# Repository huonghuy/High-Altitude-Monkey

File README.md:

# High-Altitude-Monkey (HAM)

HAM is a robotic monkey that flies on a high-altitude balloon. It moves, talks and
streams live video during flight, and is used for K-12 "near space" outreach on the
University of Bridgeport STEM bus. The project started in 2018 under a NASA USIP grant.
The 2024–2025 rebuild (HARM) adds new electronics, firmware and a controllable vent.
See the [ASEE 2025 paper](docs/papers/ASEE-2025/) for background.

## System overview

```
 Command Center ──(MC board)── Mega + HC-05 ))) Bluetooth ((( HC-05 + Mega ── ham radio ─┐
   (ground)                                                    (comms payload,          │
                                                                balloon)                │
                                                                                        │
                                                     ham-radio packets = commands       │
                                                                                        ▼
                                   HAM payload box ── Main board (Mega 2560 Pro)
                                     ├─ PCA9685 → servos (monkey movement)
                                     ├─ HC-05 ← commands from the comms payload
                                     ├─ 12 V switch → VideoLynx VM-70X video TX (on/off)
                                     └─ VL board on the VM-70X (RF power, camera, fan)
```

| Board | What it does | KiCad project |
|-------|--------------|---------------|
| **Main** | Primary board in the monkey box. Drives the servos, receives commands over Bluetooth from the comms payload, switches and controls the VideoLynx. | `hardware/kicad/Main` |
| **LM** (Land Module) | Used on the ground when HAM isn't flying. Connects the payload box to the command center over Bluetooth. | `hardware/kicad/LM` |
| **MC** (Mission Control) | Replacement for the old mission-control board in the command center. | `hardware/kicad/MC` |
| **VL** (VideoLynx) | Small board on top of the VM-70X video transmitter. Wired to Main with jumpers. | `hardware/kicad/VL` |
| **HC-05 Programmer** | Utility board for configuring the HC-05 Bluetooth modules. | `hardware/kicad/HC-05_Programmer` |

The comms payload (ham radio + Mega + HC-05) has no custom PCB.

**No HAM PCB has worked yet.** Read [`hardware/KNOWN_ISSUES.md`](hardware/KNOWN_ISSUES.md)
before ordering boards.

## Repository layout

```
hardware/
  kicad/            KiCad 10 projects (current source of truth for PCBs)
  easyeda-archive/  Original EasyEDA Standard files, all versions (read-only history)
  gerbers/          Fab outputs from past orders
  breadboard/       Early breadboard layout
  datasheets/       Part datasheets and module pinouts
  bom/              Parts list
  KNOWN_ISSUES.md   Open hardware bugs
firmware/
  Monkey_v2/            Flight firmware for the monkey (Main board, Mega 2560)
  Ground_Control/       Ground-station control sketch
  Telemetry_Processor/  Ground-side telemetry/APRS processing
  USIP_ver1_5_ESP/      ESP32 ground-station firmware (current)
  archive/              Older firmware versions (2019 USIP code, Monkey v1, USIP 1.1–1.4)
mechanical/         Body/arm STLs, MC panel (SolidWorks, 3MF, DXF)
docs/
  papers/ASEE-2025/   LaTeX source and PDF of the ASEE paper
  presentations/      Posters and slide decks (BERC 2024, NASA Minnesota, ASEE)
  flight-data/        Data from the 2025-06-05 flight
  images/             Photos, renders, diagrams
  usip-notes/         2019 USIP build notes and FAA documents
```

## Getting started

**Hardware:** Install [KiCad 10](https://www.kicad.org/) and open the `.kicad_pro` in
`hardware/kicad/<board>/`.

**Firmware (Mega boards):** Arduino IDE 2.x. Install the libraries listed in
`firmware/Monkey_v2/Libraries.txt` (Adafruit PWM Servo Driver, Adafruit BusIO), plus the
CH340 driver if you're using the Mega 2560 Pro module.

**Firmware (ESP32 ground station):** Arduino IDE with the ESP32 core. Needs Adafruit
BME280 and Adafruit Unified Sensor. See the notes at the top of
`firmware/USIP_ver1_5_ESP/USIP_ver1_5/Config.h`.

## Large files

Slide decks (`*.pptx`) are stored with [Git LFS](https://git-lfs.com). Run
`git lfs install` before cloning, or you'll get small pointer files instead of the decks.

## License

See [LICENSE](LICENSE).

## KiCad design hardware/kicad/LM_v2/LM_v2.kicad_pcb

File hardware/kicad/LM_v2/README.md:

# LM_v2: Land Module (ESP32)

Bluetooth Classic ↔ RS-232 bridge between the comms payload and Mission Control, built on an ESP32-WROOM-32E. It replaces the old ATmega2560 + HC-05 LM. Firmware is in `firmware/LM_v2`.

## Projects

| Project | Board |
|---|---|
| `LM_v2` | 36 × 55.3 mm, plus two M3 mounting ears (52 mm across) |
| `LM_v2_NoMount` | Same board, 36 × 55.3 mm, no ears |

`LM_v2.kicad_sch` is the master. `LM_v2_NoMount.kicad_sch` is a copy, and the NoMount PCB is LM_v2's board with the ears and M3 holes removed. After a change, copy both over and re-derive NoMount.

## Design notes

- Power: USB-C VBUS → PTC fuse F1 → TPS62162 3.3 V buck (U4, 2.2 µH L1, 10 µF in, 22 µF out). The buck is routed to TI's layout guide (SLVSAM2E §11). VOS senses +3V3 at C2.
- USB-UART: CH340C with two-transistor auto-reset into EN and IO0. USBLC6-2 ESD on the data lines.
- RS-232: MAX3232 to J2, an Assmann A-DS 09 A/KG-T2S (`HAM:DSUB-9_Male_Horizontal_Assmann_A-DS-KG`, drawing ASS 4888 CO in `hardware/datasheets/`). It is centred on the bottom edge with its two boardlock holes (Ø3.05 mm, 24.99 mm apart); the board edge sits at the flange, 7.2 mm from the pin 6–9 row.
- The ESP32 antenna overhangs the top edge. Keep metal away from it in the enclosure.
- Trace widths: 0.4 mm power class (VBUS, +3V3, GND), 0.2 mm signals, GND pours on both layers with stitching vias.

## Checks

Run from `hardware/kicad`:

```
python3 tools/check_netlist.py LM_v2/LM_v2.kicad_sch LM_v2/pin_nets.csv   # every pin's net vs the design table
kicad-cli sch erc LM_v2/LM_v2.kicad_sch
kicad-cli pcb drc --schematic-parity LM_v2/LM_v2.kicad_pcb
```

All three were clean on 2026-11-25. If you change a net on purpose, update `pin_nets.csv` as well.

## Connection to Mission Control

J2 plugs into MC's Telemetry Processor port (`Serial2`, a female DE-9 described in the firmware as "PC, for telemetry Processor"), either directly or through the existing 6 ft male-to-female cable. J2 is a male DE-9 wired like a PC: pin 2 = LM receive, pin 3 = LM transmit, pin 5 = GND. This matches the ground-station setup in `docs/` (the grey box next to the Command Processor).

## Parts

Every part has a manufacturer and part number in the schematic (`Manufacturer`, `MPN` fields). The boards are hand-assembled. U4 (TPS62162, WSON) and the ESP32's ground pad both need hot air or the hotplate. TP1–TP3 are bare pads and are not on the BOM.

## Open before ordering

Fab packages (Gerbers, drill, BOM, assembly PDFs) are in `hardware/gerbers/LM_v2/` and `hardware/gerbers/LM_v2_NoMount/`.

- **J2 footprint:** drawn from the Assmann drawing, reading its "7.2 mm footprint" as board edge to the pin 6–9 row. Check it against a real connector before a large order.
- **Bluetooth pairing:** the firmware waits as a slave, so the payload HC-05 has to be set as master and bound to the LM's address. See `firmware/LM_v2/README.md`.
- **Board-level details:** R2's reference label is on the Fab layer only, because the silkscreen had no room for it.

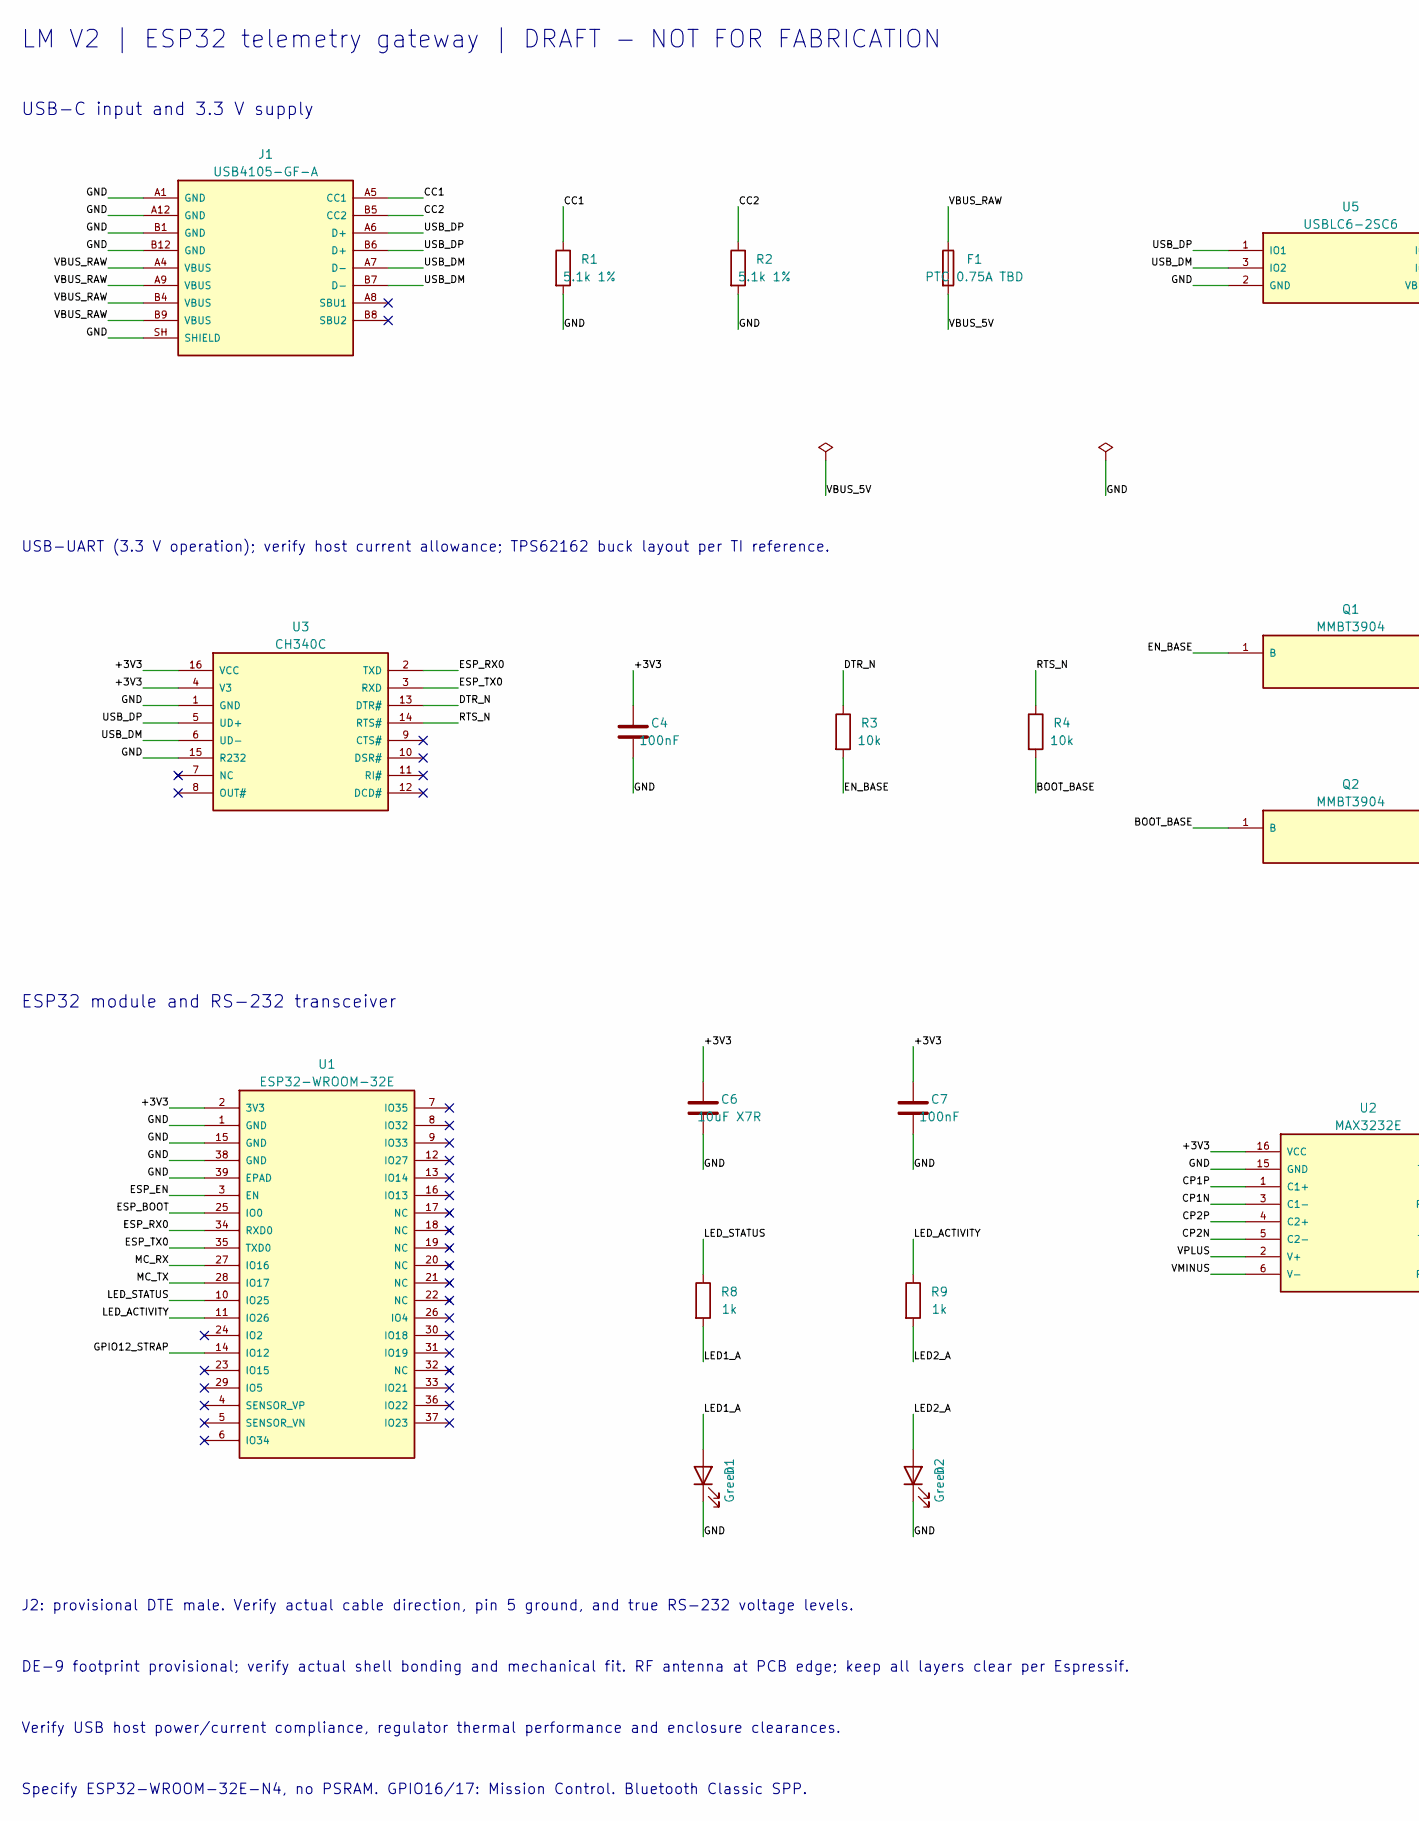
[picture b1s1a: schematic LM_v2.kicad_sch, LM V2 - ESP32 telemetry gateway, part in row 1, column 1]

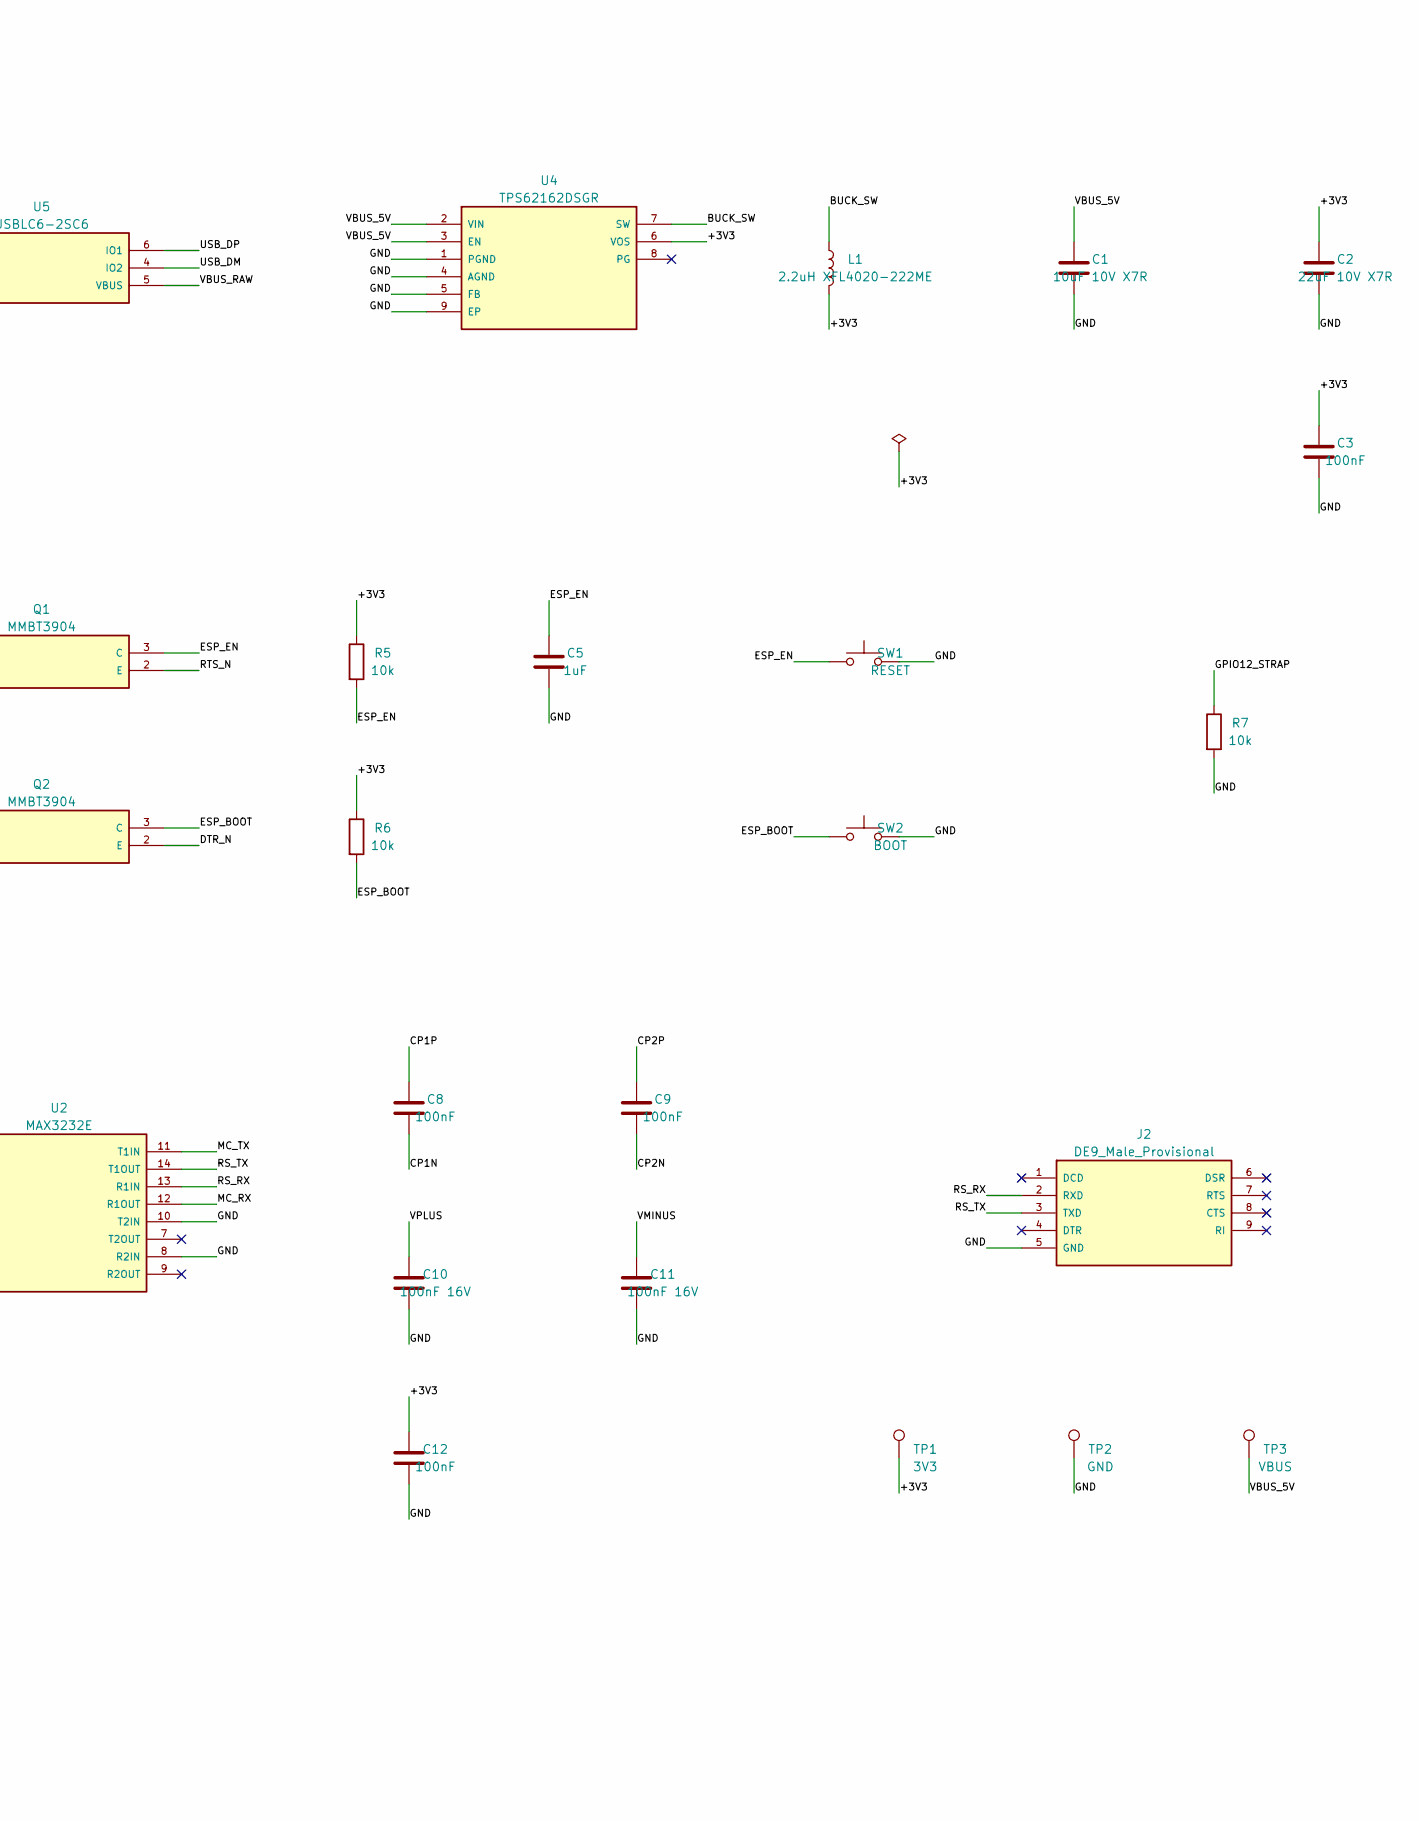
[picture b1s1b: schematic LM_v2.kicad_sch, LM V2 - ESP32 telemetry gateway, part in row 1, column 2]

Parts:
C1: 10uF 10V X7R; C_0805_2012Metric
C2: 22uF 10V X7R; C_1206_3216Metric
C3, C4, C7, C8, C9, C12: 100nF; C_0603_1608Metric
C5: 1uF; C_0603_1608Metric
C6: 10uF X7R; C_0805_2012Metric
C10, C11: 100nF 16V; C_0603_1608Metric
D1, D2: Green; LED_0603_1608Metric
F1: PTC 0.75A TBD; Fuse_1206_3216Metric
J1: USB4105-GF-A; USB_C_Receptacle_GCT_USB4105-xx-A_16P_TopMnt_Horizontal
J2: DE9_Male_Provisional; DSUB-9_Male_Horizontal_BoardEdge
L1: 2.2uH XFL4020-222ME; L_Coilcraft_XxL4020
Q1, Q2: MMBT3904; SOT-23
R1, R2: 5.1k 1%; R_0603_1608Metric
R3, R4, R5, R6, R7: 10k; R_0603_1608Metric
R8, R9: 1k; R_0603_1608Metric
SW1: RESET; SW_SPST_TL3342
SW2: BOOT; SW_SPST_TL3342
TP1: 3V3; TestPoint_Pad_D1.5mm
TP2: GND; TestPoint_Pad_D1.5mm
TP3: VBUS; TestPoint_Pad_D1.5mm
U1: ESP32-WROOM-32E
U2: MAX3232E; SOIC-16_3.9x9.9mm_P1.27mm
U3: CH340C; SOIC-16_3.9x9.9mm_P1.27mm
U4: TPS62162DSGR; WSON-8-1EP_2x2mm_P0.5mm_EP0.9x1.6mm_ThermalVias
U5: USBLC6-2SC6; SOT-23-6

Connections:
/+3V3: C2.1, C3.1, C4.1, C6.1, C7.1, C12.1, L1.2, R5.1, R6.1, TP1.1 (1_1), U1.2 (3V3), U2.16 (VCC), U3.4 (V3), U3.16 (VCC), U4.6 (VOS)
/BOOT_BASE: Q2.1 (B), R4.2
/BUCK_SW: L1.1, U4.7 (SW)
/CC1: J1.A5 (CC1), R1.1
/CC2: J1.B5 (CC2), R2.1
/CP1N: C8.2, U2.3 (C1-)
/CP1P: C8.1, U2.1 (C1+)
/CP2N: C9.2, U2.5 (C2-)
/CP2P: C9.1, U2.4 (C2+)
/DTR_N: Q2.2 (E), R3.1, U3.13 (DTR#)
/EN_BASE: Q1.1 (B), R3.2
/ESP_BOOT: Q2.3 (C), R6.2, SW2.1, U1.25 (IO0)
/ESP_EN: C5.1, Q1.3 (C), R5.2, SW1.1, U1.3 (EN)
/ESP_RX0: U1.34 (RXD0), U3.2 (TXD)
/ESP_TX0: U1.35 (TXD0), U3.3 (RXD)
/GND: C1.2, C2.2, C3.2, C4.2, C5.2, C6.2, C7.2, C10.2, C11.2, C12.2, D1.1 (K), D2.1 (K), J1.A1 (GND), J1.A12 (GND), J1.B1 (GND), J1.B12 (GND), J1.SH (SHIELD), J2.5 (GND), R1.2, R2.2, R7.2, SW1.2, SW2.2, TP2.1 (1_1), U1.1 (GND), U1.15 (GND), U1.38 (GND), U1.39 (EPAD), U2.8 (R2IN), U2.10 (T2IN), U2.15 (GND), U3.1 (GND), U3.15 (R232), U4.1 (PGND), U4.4 (AGND), U4.5 (FB), U4.9 (EP), U5.2 (GND)
/GPIO12_STRAP: R7.1, U1.14 (IO12)
/LED1_A: D1.2 (A), R8.2
/LED2_A: D2.2 (A), R9.2
/LED_ACTIVITY: R9.1, U1.11 (IO26)
/LED_STATUS: R8.1, U1.10 (IO25)
/MC_RX: U1.27 (IO16), U2.12 (R1OUT)
/MC_TX: U1.28 (IO17), U2.11 (T1IN)
/RS_RX: J2.2 (RXD), U2.13 (R1IN)
/RS_TX: J2.3 (TXD), U2.14 (T1OUT)
/RTS_N: Q1.2 (E), R4.1, U3.14 (RTS#)
/USB_DM: J1.A7 (D-), J1.B7 (D-), U3.6 (UD-), U5.3 (IO2), U5.4 (IO2)
/USB_DP: J1.A6 (D+), J1.B6 (D+), U3.5 (UD+), U5.1 (IO1), U5.6 (IO1)
/VBUS_5V: C1.1, F1.2, TP3.1 (1_1), U4.2 (VIN), U4.3 (EN)
/VBUS_RAW: F1.1, J1.A4 (VBUS), J1.A9 (VBUS), J1.B4 (VBUS), J1.B9 (VBUS), U5.5 (VBUS)
/VMINUS: C11.1, U2.6 (V-)
/VPLUS: C10.1, U2.2 (V+)

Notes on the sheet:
J2: provisional DTE male. Verify actual cable direction, pin 5 ground, and true RS-232 voltage levels.
USB-UART (3.3 V operation); verify host current allowance; TPS62162 buck layout per TI reference.
USB-C input and 3.3 V supply
Specify ESP32-WROOM-32E-N4, no PSRAM. GPIO16/17: Mission Control. Bluetooth Classic SPP.
ESP32 module and RS-232 transceiver
DE-9 footprint provisional; verify actual shell bonding and mechanical fit. RF antenna at PCB edge; keep all layers clear per Espressif.
LM V2 | ESP32 telemetry gateway | DRAFT - NOT FOR FABRICATION
Verify USB host power/current compliance, regulator thermal performance and enclosure clearances.

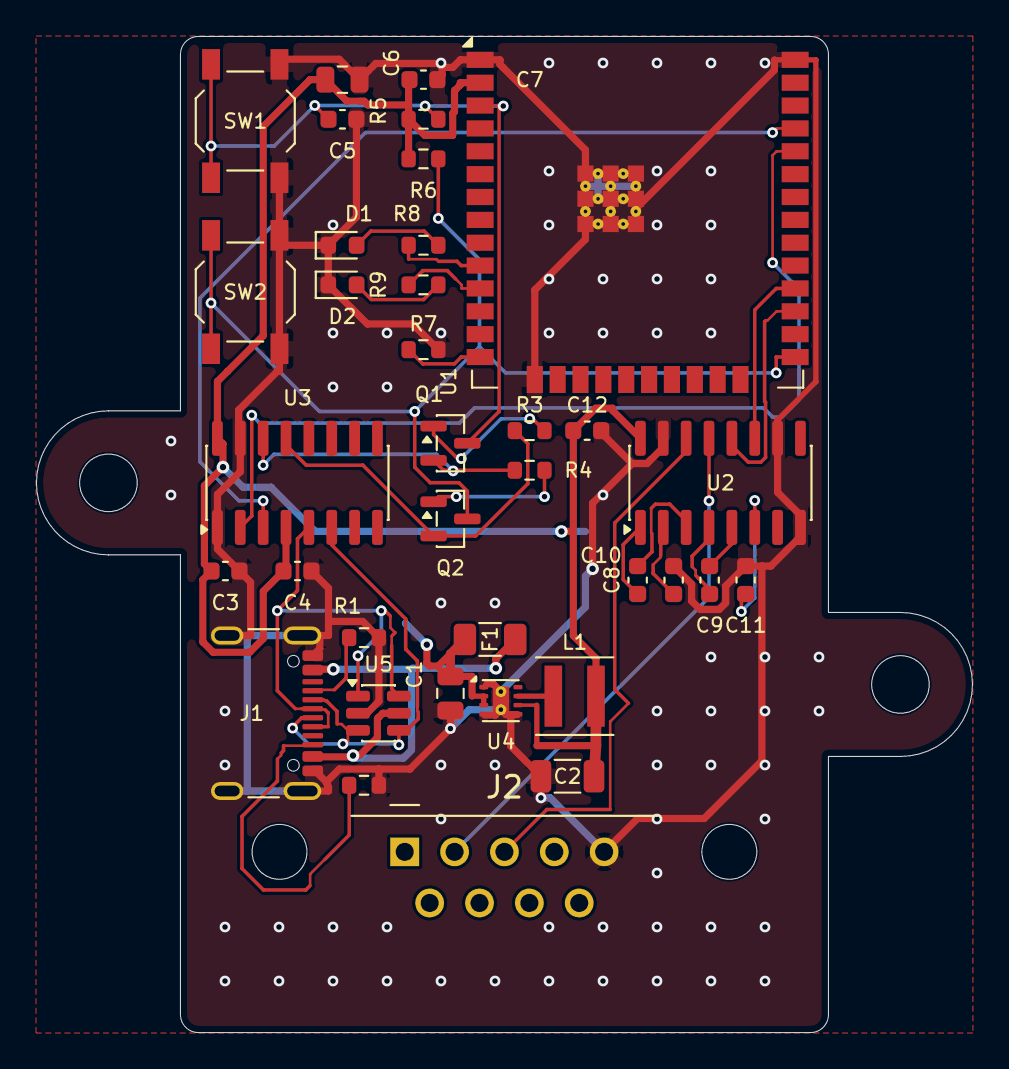
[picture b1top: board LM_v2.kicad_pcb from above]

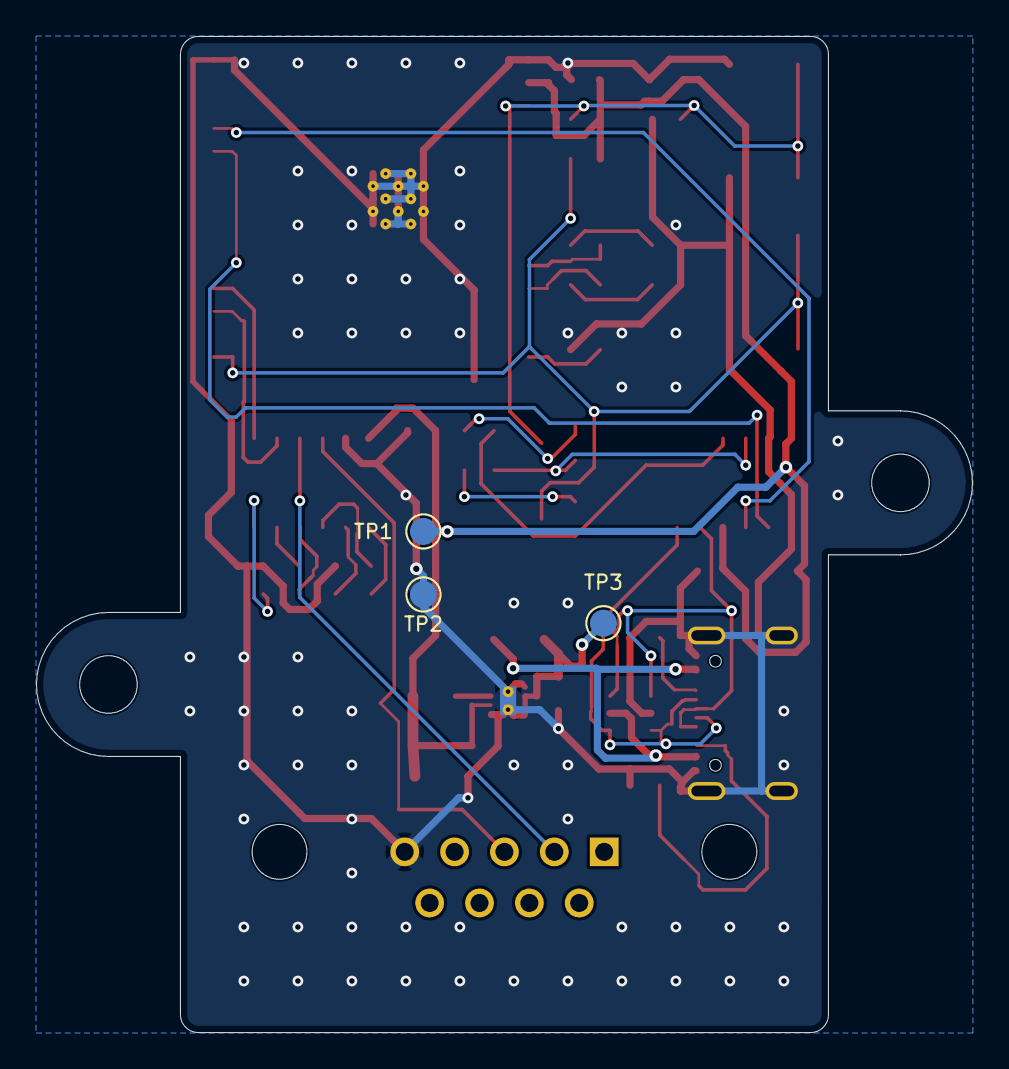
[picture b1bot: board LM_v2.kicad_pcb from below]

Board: 2 copper layers, 52.0 x 55.3 mm, 41 parts (3 on the bottom side), 32 nets.

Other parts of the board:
H1, H2: M3; MountingHole_3.2mm_M3

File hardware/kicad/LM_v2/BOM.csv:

Reference,Value,Footprint,Fit
J1,USB4105-GF-A,Connector_USB:USB_C_Receptacle_GCT_USB4105-xx-A_16P_TopMnt_Horizontal,Fit
R1,5.1k 1%,Resistor_SMD:R_0603_1608Metric,Fit
R2,5.1k 1%,Resistor_SMD:R_0603_1608Metric,Fit
F1,PTC 0.75A TBD,Fuse:Fuse_1206_3216Metric,Fit
U5,USBLC6-2SC6,Package_TO_SOT_SMD:SOT-23-6,Fit
U4,TPS62162DSGR,Package_SON:WSON-8-1EP_2x2mm_P0.5mm_EP0.9x1.6mm_ThermalVias,Fit
L1,2.2uH XFL4020-222ME,Inductor_SMD:L_Coilcraft_XxL4020,Fit
C1,10uF 10V X7R,Capacitor_SMD:C_0805_2012Metric,Fit
C2,22uF 10V X7R,Capacitor_SMD:C_1206_3216Metric,Fit
C3,100nF,Capacitor_SMD:C_0603_1608Metric,Fit
U3,CH340C,Package_SO:SOIC-16_3.9x9.9mm_P1.27mm,Fit
C4,100nF,Capacitor_SMD:C_0603_1608Metric,Fit
R3,10k,Resistor_SMD:R_0603_1608Metric,Fit
R4,10k,Resistor_SMD:R_0603_1608Metric,Fit
Q1,MMBT3904,Package_TO_SOT_SMD:SOT-23,Fit
Q2,MMBT3904,Package_TO_SOT_SMD:SOT-23,Fit
R5,10k,Resistor_SMD:R_0603_1608Metric,Fit
R6,10k,Resistor_SMD:R_0603_1608Metric,Fit
C5,1uF,Capacitor_SMD:C_0603_1608Metric,Fit
SW1,RESET,Button_Switch_SMD:SW_SPST_TL3342,Fit
SW2,BOOT,Button_Switch_SMD:SW_SPST_TL3342,Fit
R7,10k,Resistor_SMD:R_0603_1608Metric,Fit
U1,ESP32-WROOM-32E,RF_Module:ESP32-WROOM-32E,Fit
C6,10uF X7R,Capacitor_SMD:C_0805_2012Metric,Fit
C7,100nF,Capacitor_SMD:C_0603_1608Metric,Fit
R8,1k,Resistor_SMD:R_0603_1608Metric,Fit
R9,1k,Resistor_SMD:R_0603_1608Metric,Fit
D1,Green,LED_SMD:LED_0603_1608Metric,Fit
D2,Green,LED_SMD:LED_0603_1608Metric,Fit
U2,MAX3232E,Package_SO:SOIC-16_3.9x9.9mm_P1.27mm,Fit
C8,100nF,Capacitor_SMD:C_0603_1608Metric,Fit
C9,100nF,Capacitor_SMD:C_0603_1608Metric,Fit
C10,100nF 16V,Capacitor_SMD:C_0603_1608Metric,Fit
C11,100nF 16V,Capacitor_SMD:C_0603_1608Metric,Fit
C12,100nF,Capacitor_SMD:C_0603_1608Metric,Fit
J2,DE9_Male_Provisional,Connector_Dsub:DSUB-9_Pins_Horizontal_P2.77x2.84mm_EdgePinOffset9.40mm,Fit
TP1,3V3,TestPoint:TestPoint_Pad_D1.5mm,Fit
TP2,GND,TestPoint:TestPoint_Pad_D1.5mm,Fit
TP3,VBUS,TestPoint:TestPoint_Pad_D1.5mm,Fit

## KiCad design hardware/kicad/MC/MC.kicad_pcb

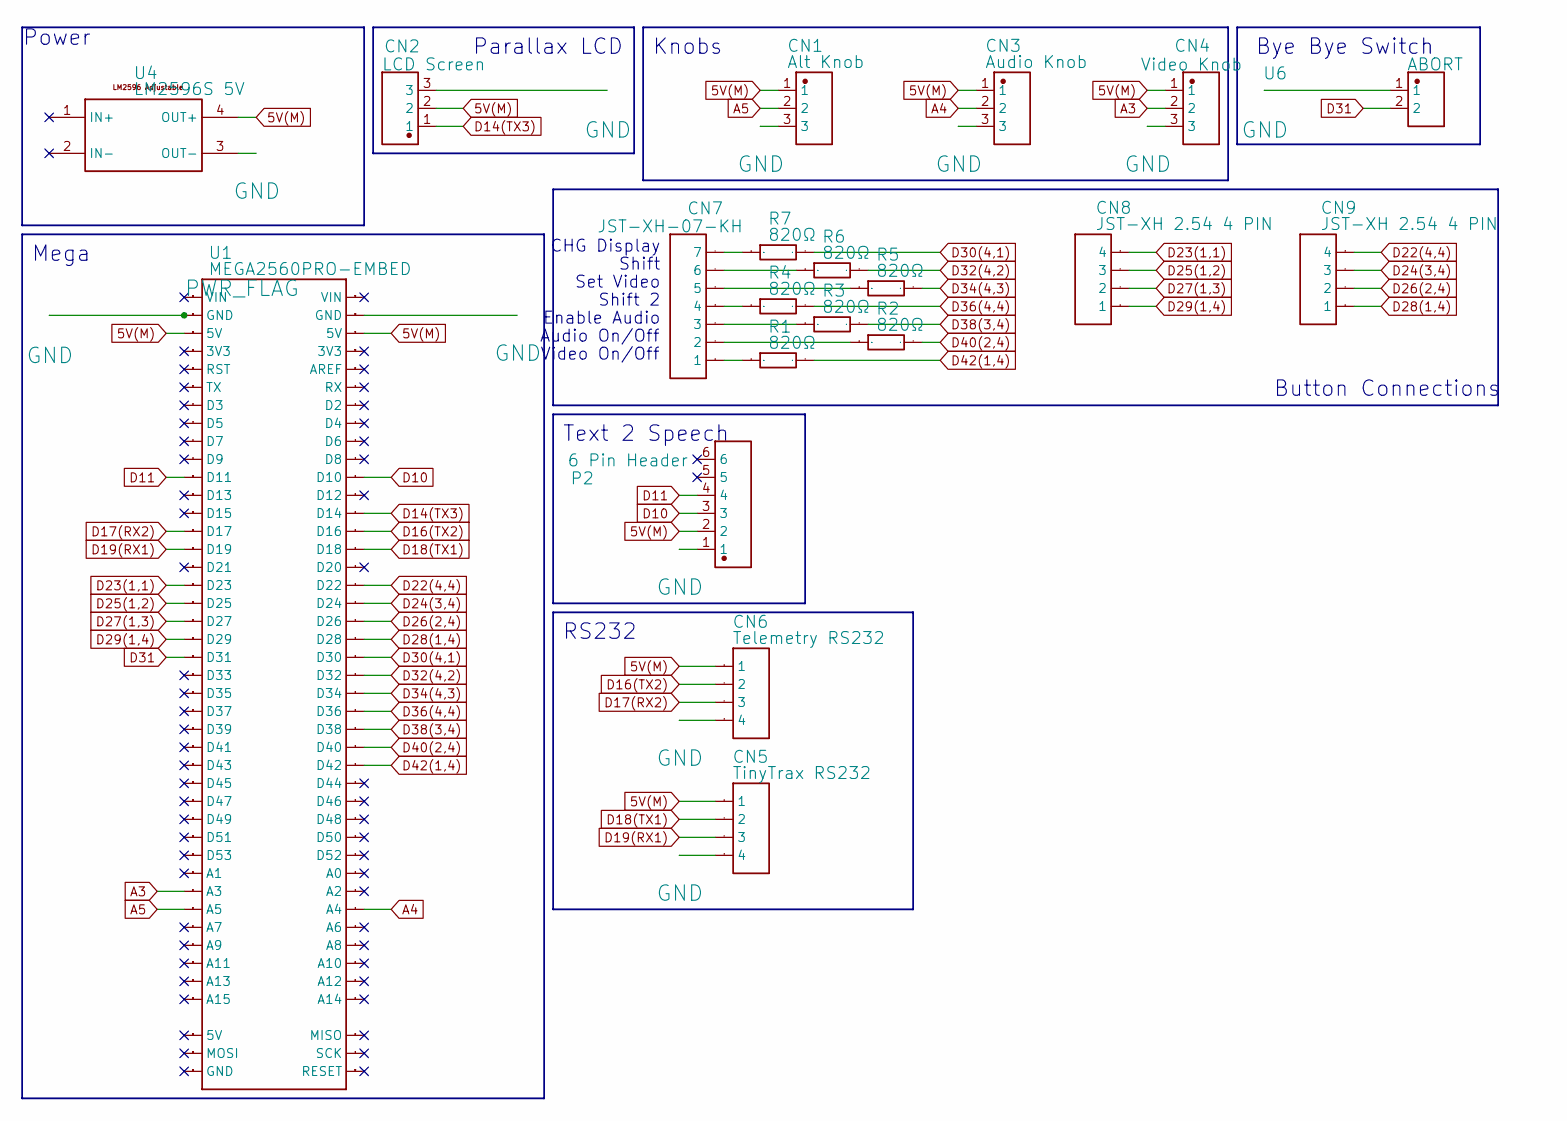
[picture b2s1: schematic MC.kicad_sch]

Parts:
CN1: Alt Knob; JST_XH_B3B-XH-A_1x03_P2.50mm_Vertical; Manufacturer Part XH插座1*3P间距2.5mm直针,
CN2: LCD Screen; JST_XH_B3B-XH-A_1x03_P2.50mm_Vertical; Manufacturer Part XH插座1*3P间距2.5mm直针,
CN3: Audio Knob; JST_XH_B3B-XH-A_1x03_P2.50mm_Vertical; Manufacturer Part XH插座1*3P间距2.5mm直针,
CN4: Video Knob; JST_XH_B3B-XH-A_1x03_P2.50mm_Vertical; Manufacturer Part XH插座1*3P间距2.5mm直针,
CN5: TinyTrax RS232; JST_XH_B4B-XH-A_1x04_P2.50mm_Vertical
CN6: Telemetry RS232; JST_XH_B4B-XH-A_1x04_P2.50mm_Vertical
CN7: JST-XH-07-KH; JST_XH_B7B-XH-A_1x07_P2.50mm_Vertical; Manufacturer Part JST-XH-04
CN8, CN9: JST-XH 2.54 4 PIN; JST_XH_B4B-XH-A_1x04_P2.50mm_Vertical
P2: 6 Pin Header; PinSocket_1x06_P2.54mm_Vertical; Manufacturer Part 2.54-1*6P母
R1, R2, R3, R4, R5, R6, R7: 820Ω; R_0402_1005Metric; Manufacturer Part RC0402JR-07820RL
U1: MEGA2560PRO-EMBED; Mega2560_Pro_Embed
U4: LM2596S 5V; LM2596_Module
U6: ABORT; JST_XH_B2B-XH-A_1x02_P2.50mm_Vertical; Manufacturer Part XH-2P-2.54

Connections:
5V(M): CN1.1, CN2.2, CN3.1, CN4.1, CN5.1, CN6.1, P2.2, U1.5V@1 (5V), U1.5V@2 (5V), U4.4 (OUT+)
A3: CN4.2, U1.A3
A4: CN3.2, U1.A4
A5: CN1.2, U1.A5
D10: P2.3, U1.D10
D11: P2.4, U1.D11
D14(TX3): CN2.1, U1.D14
D16(TX2): CN6.2, U1.D16
D17(RX2): CN6.3, U1.D17
D18(TX1): CN5.2, U1.D18
D19(RX1): CN5.3, U1.D19
D22(4,4): CN9.4, U1.D22
D23(1,1): CN8.4, U1.D23
D24(3,4): CN9.3, U1.D24
D25(1,2): CN8.3, U1.D25
D26(2,4): CN9.2, U1.D26
D27(1,3): CN8.2, U1.D27
D28(1,4): CN9.1, U1.D28
D29(1,4): CN8.1, U1.D29
D30(4,1): R7.2, U1.D30
D31: U1.D31, U6.2
D32(4,2): R6.2, U1.D32
D34(4,3): R5.2, U1.D34
D36(4,4): R4.2, U1.D36
D38(3,4): R3.2, U1.D38
D40(2,4): R2.2, U1.D40
D42(1,4): R1.2, U1.D42
GND: CN1.3, CN2.3, CN3.3, CN4.3, CN5.4, CN6.4, P2.1, U1.GND@1 (GND), U1.GND@2 (GND), U4.3 (OUT-), U6.1
unnamed: CN7.1, R1.1
unnamed: CN7.2, R2.1
unnamed: CN7.3, R3.1
unnamed: CN7.4, R4.1
unnamed: CN7.5, R5.1
unnamed: CN7.6, R6.1
unnamed: CN7.7, R7.1

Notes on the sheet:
Knobs
Video On/Off
Parallax LCD
RS232
Set Video
Button Connections
Shift
Bye Bye Switch
Shift 2
Text 2 Speech
Power
Enable Audio
Mega
CHG Display
Audio On/Off

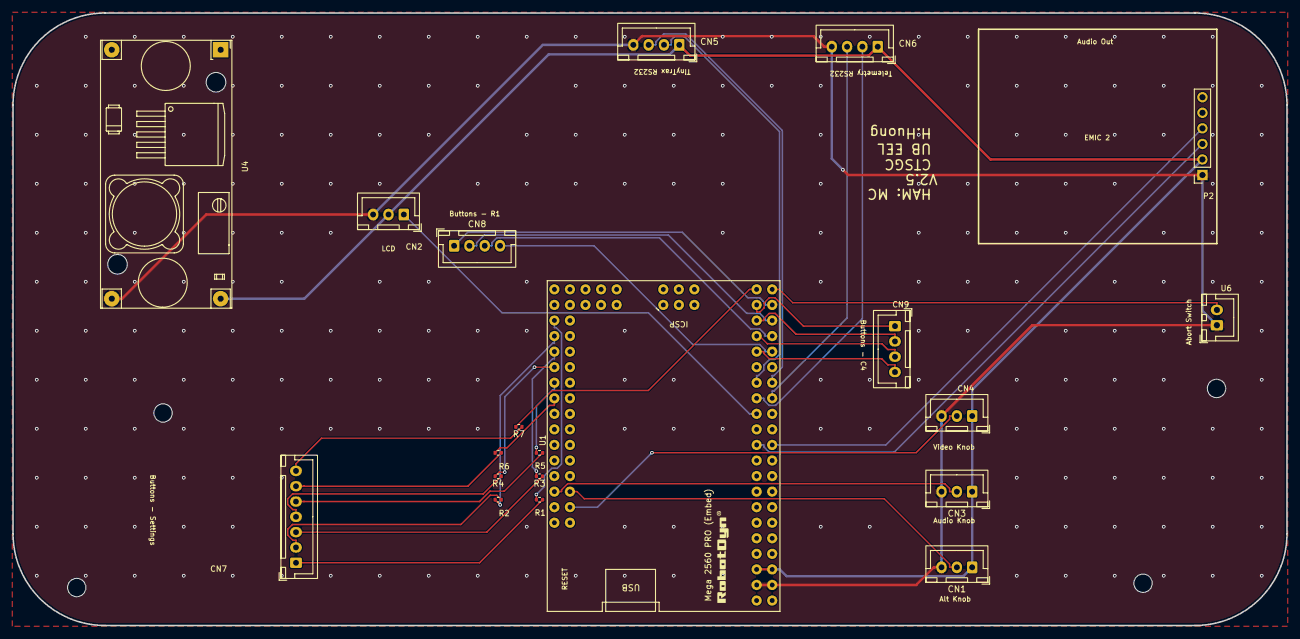
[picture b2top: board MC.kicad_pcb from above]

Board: 2 copper layers, 208.0 x 100.0 mm, 24 parts (0 on the bottom side), 35 nets.

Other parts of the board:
H2, H3, H4, H6: Hole 3mm; MountingHole_3mm

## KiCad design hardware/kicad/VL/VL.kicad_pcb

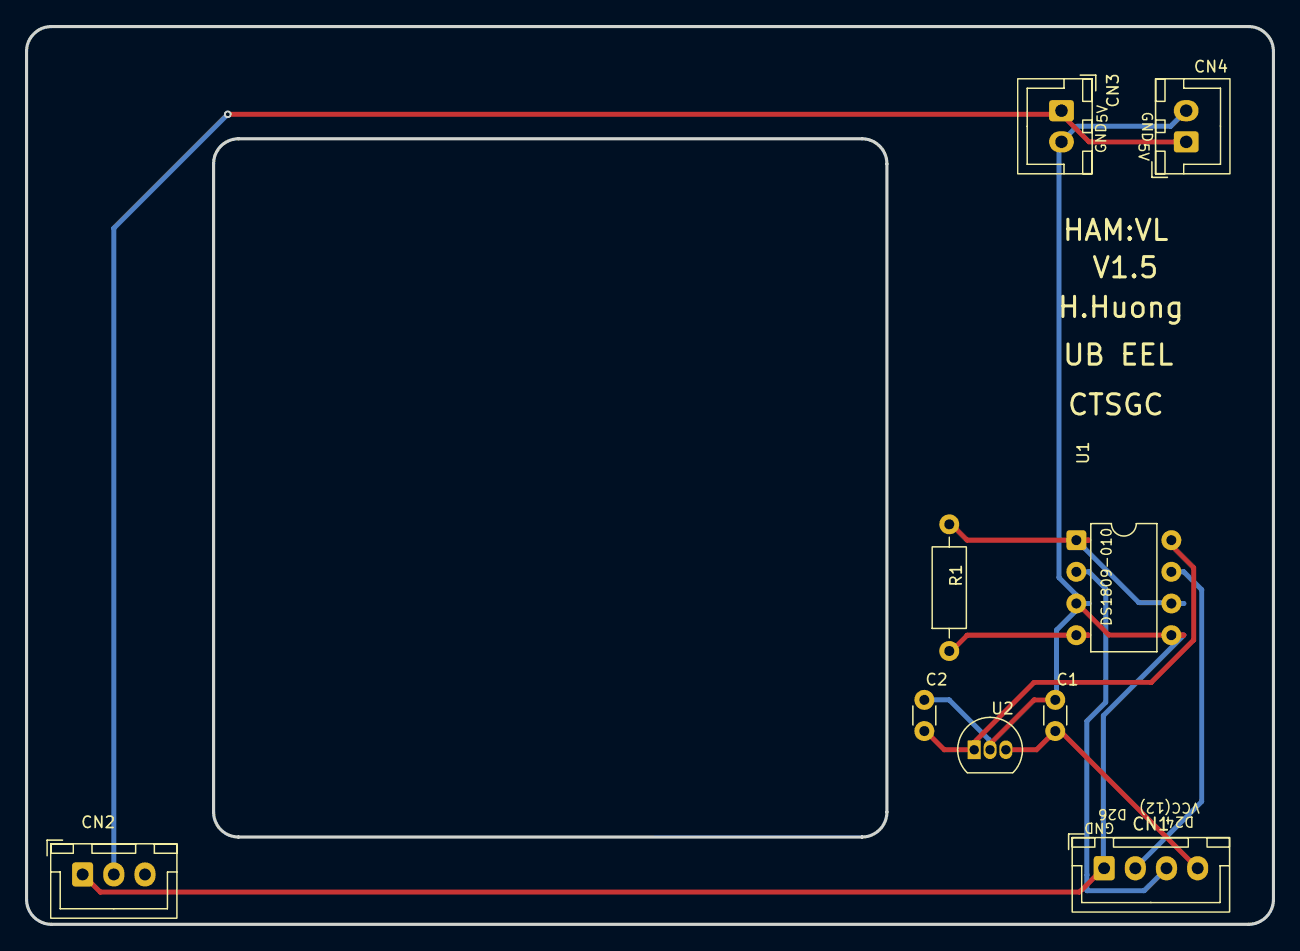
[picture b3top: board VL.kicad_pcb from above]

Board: 2 copper layers, 100.0 x 72.0 mm, 9 parts (0 on the bottom side), 8 nets.

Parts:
C1: 0.33uF; C_Disc_D3.0mm_W1.6mm_P2.50mm
C2: 0.1uF; C_Disc_D3.0mm_W1.6mm_P2.50mm
CN1: JST-XH2.5; JST_XH_B4B-XH-A_1x04_P2.50mm_Vertical
CN2: VideoLynx Fan; JST_XH_B3B-XH-A_1x03_P2.50mm_Vertical
CN3: Camera; JST_XH_B2B-XH-A_1x02_P2.50mm_Vertical
CN4: VL Power; JST_XH_B2B-XH-A_1x02_P2.50mm_Vertical
R1: 12kΩ; R_Axial_DIN0207_L6.3mm_D2.5mm_P10.16mm_Horizontal
U1: DS1809-010 10k Digital Pot; DIP-8_W7.62mm
U2: L78L05 (5 V, 100 mA); TO-92_Inline

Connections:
/5V: CN2.2, CN3.1, CN4.1
/5V_DS: C2.1, U1.8, U2.1
/D24: CN1.3, U1.2
/D26: CN1.2, U1.7
/VCC(12): C1.1, CN1.4, U2.3
GND: C1.2, C2.2, CN1.1, CN2.1, CN3.2, CN4.2, U1.3, U1.5, U2.2
unnamed: R1.2, U1.1, U1.6
unnamed: R1.1, U1.4

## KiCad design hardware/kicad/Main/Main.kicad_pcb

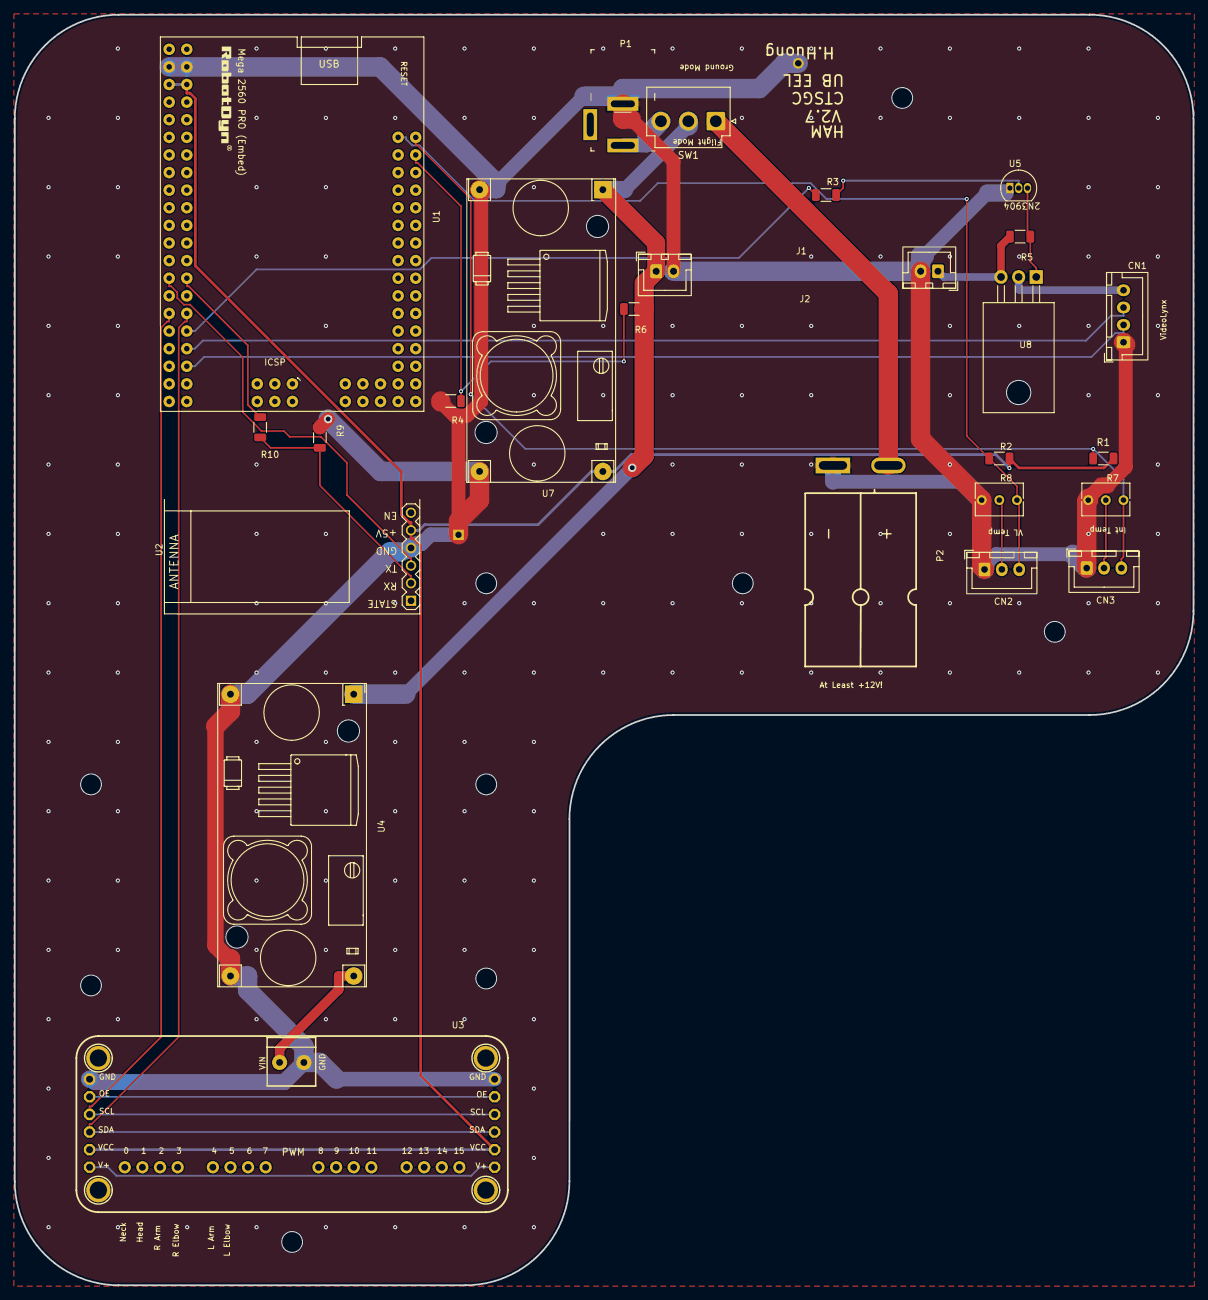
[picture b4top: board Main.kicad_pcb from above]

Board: 2 copper layers, 170.0 x 183.2 mm, 36 parts (0 on the bottom side), 23 nets.

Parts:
CN1: JST-XH2.5; JST_XH_B4B-XH-A_1x04_P2.50mm_Vertical
CN2: VideoLynx LM135H; JST_XH_B3B-XH-A_1x03_P2.50mm_Vertical
CN3: Int LM135H; JST_XH_B3B-XH-A_1x03_P2.50mm_Vertical
H1, H2, H3, H4, H7, H9, H10, H11, H12: Hole 3mm; MountingHole_3mm
J1: Pololu IN; JST_XH_B2B-XH-A_1x02_P2.50mm_Vertical
J2: Pololu OUT 13V; JST_XH_B2B-XH-A_1x02_P2.50mm_Vertical
P1: DC barrel jack 2.1mm; DC_Barrel_Jack_2.1mm
P2: PowerPole; Anderson_PowerPole_1327_Pair_Horizontal
R1, R2: 1.5kΩ; R_1206_3216Metric
R3: 3.3kΩ; R_1206_3216Metric
R4: 3.9kΩ; R_1206_3216Metric
R5: 8.2kΩ; R_1206_3216Metric
R6: 10kΩ; R_1206_3216Metric
R7, R8: 10kΩ; Potentiometer_Bourns_3266Y_Vertical
R9: 2kΩ; R_1206_3216Metric
R10: 1kΩ; R_1206_3216Metric
SW1: ON-OFF-ON Toggle (off-board); JST_VH_B3P-VH_1x03_P3.96mm_Vertical
U1: MEGA2560PRO-EMBED; Mega2560_Pro_Embed
U2: HC-05; HC-05_Module
U3: PCA9685; PCA9685_Breakout_Adafruit
U4: LM2596S 6V; LM2596_Module
U5: 2N3904; TO-92_Inline
U7: LM2596S 5V; LM2596_Module
U8: IRF9540N_FLAT; TO-220-3_Horizontal_TabDown
WP1: Wire pad; Pad_THT_Wire_D0.96mm
WP2: Wire pad; Pad_THT_Wire_D0.91mm

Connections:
5V(M): R1.1, R2.1, U1.5V@1, U1.5V@2, U2.5, U3.7 (VCC), U7.4
A0: CN3.3, R1.2, R7.3, U1.A0
A1: CN2.3, R2.2, R8.3, U1.A1
A2: R4.2, R6.2, U1.A2
D16(TX2): R10.1, U1.D16
D17(RX2): U1.D17, U2.3
D20(SDA): U1.D20, U3.6 (SDA)
D21(SCL): U1.D21, U3.5 (SCL)
D22: R3.1, U1.D22
D24: CN1.3, U1.D24
D26: CN1.2, U1.D26
GND: CN1.1, CN2.1, CN3.1, J1.2, J2.2, P1.2, P2.1, R4.1, R7.1, R8.1, R9.1, U1.GND@1, U1.GND@2, U2.4, U3.2 (GND), U3.3 (GND), U4.2, U4.3, U5.1 (E), U7.2, U7.3, WP1.2, WP2.1
unnamed: CN2.2, R8.2
unnamed: CN3.2, R7.2
unnamed: P2.2, SW1.1
unnamed: P1.1, SW1.3
unnamed: R9.2, R10.2, U2.2
unnamed: R3.2, U5.2 (B)
unnamed: R5.1, U5.3 (C), U8.1 (G)
Switch(12): CN1.4, U8.2 (D)
VCC: J1.1, R6.1, SW1.2, U4.1, U7.1
VCC(6): U3.1 (VIN), U4.4
VCC(12): J2.1, R5.2, U8.3 (S)

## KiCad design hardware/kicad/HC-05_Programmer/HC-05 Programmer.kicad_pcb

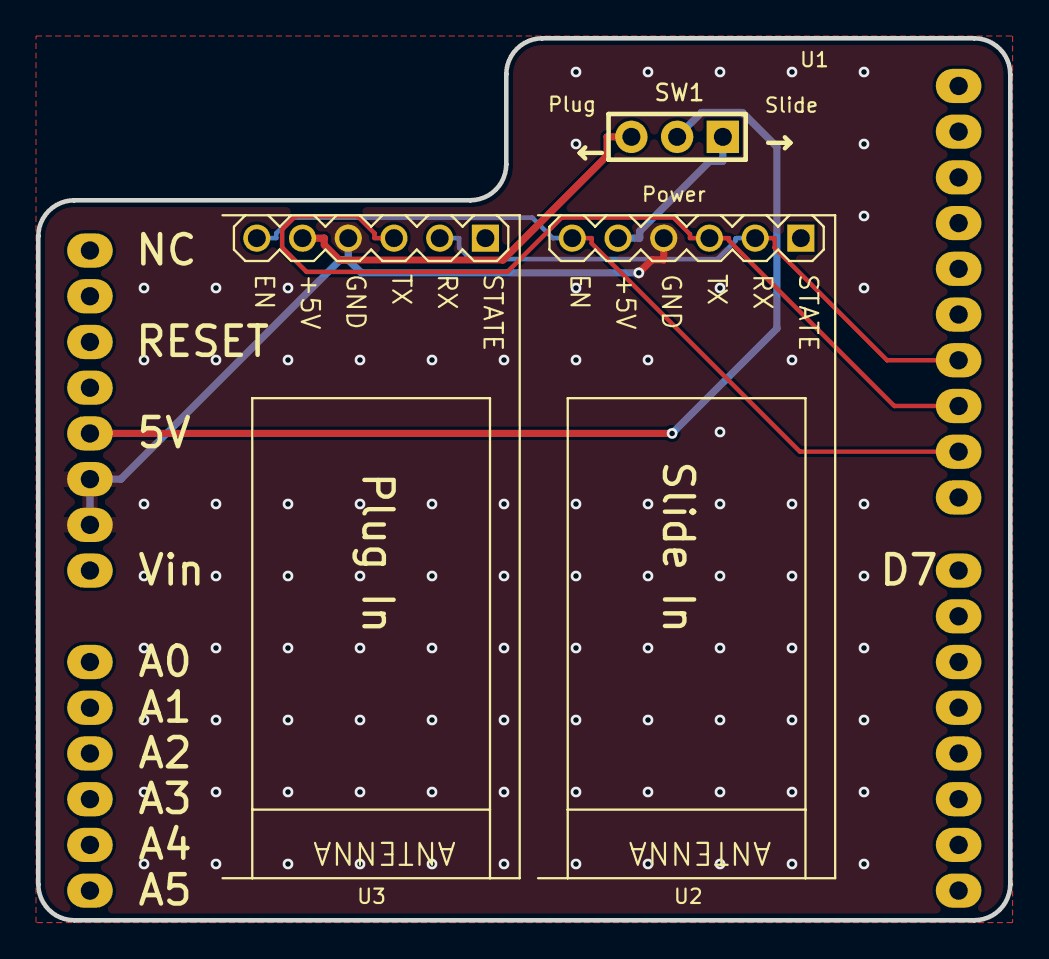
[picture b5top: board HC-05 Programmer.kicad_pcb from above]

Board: 2 copper layers, 54.0 x 49.0 mm, 4 parts (0 on the bottom side), 7 nets.

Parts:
SW1: SPST Toggle; Toggle_Switch_SPDT_Wire_Pads
U1: ArduinoUnoR3_Custom; Arduino_Uno_R3_Shield
U2, U3: HC-05; HC-05_Module

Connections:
+5V: SW1.2, U1.5
D9: U1.24, U2.6, U3.6
D10: U1.25, U2.3, U3.3
D11: U1.26, U2.2, U3.2
GND: U1.6, U1.7, U2.4, U3.4
PlugIn: SW1.3, U3.5
SlideIn: SW1.1, U2.5
